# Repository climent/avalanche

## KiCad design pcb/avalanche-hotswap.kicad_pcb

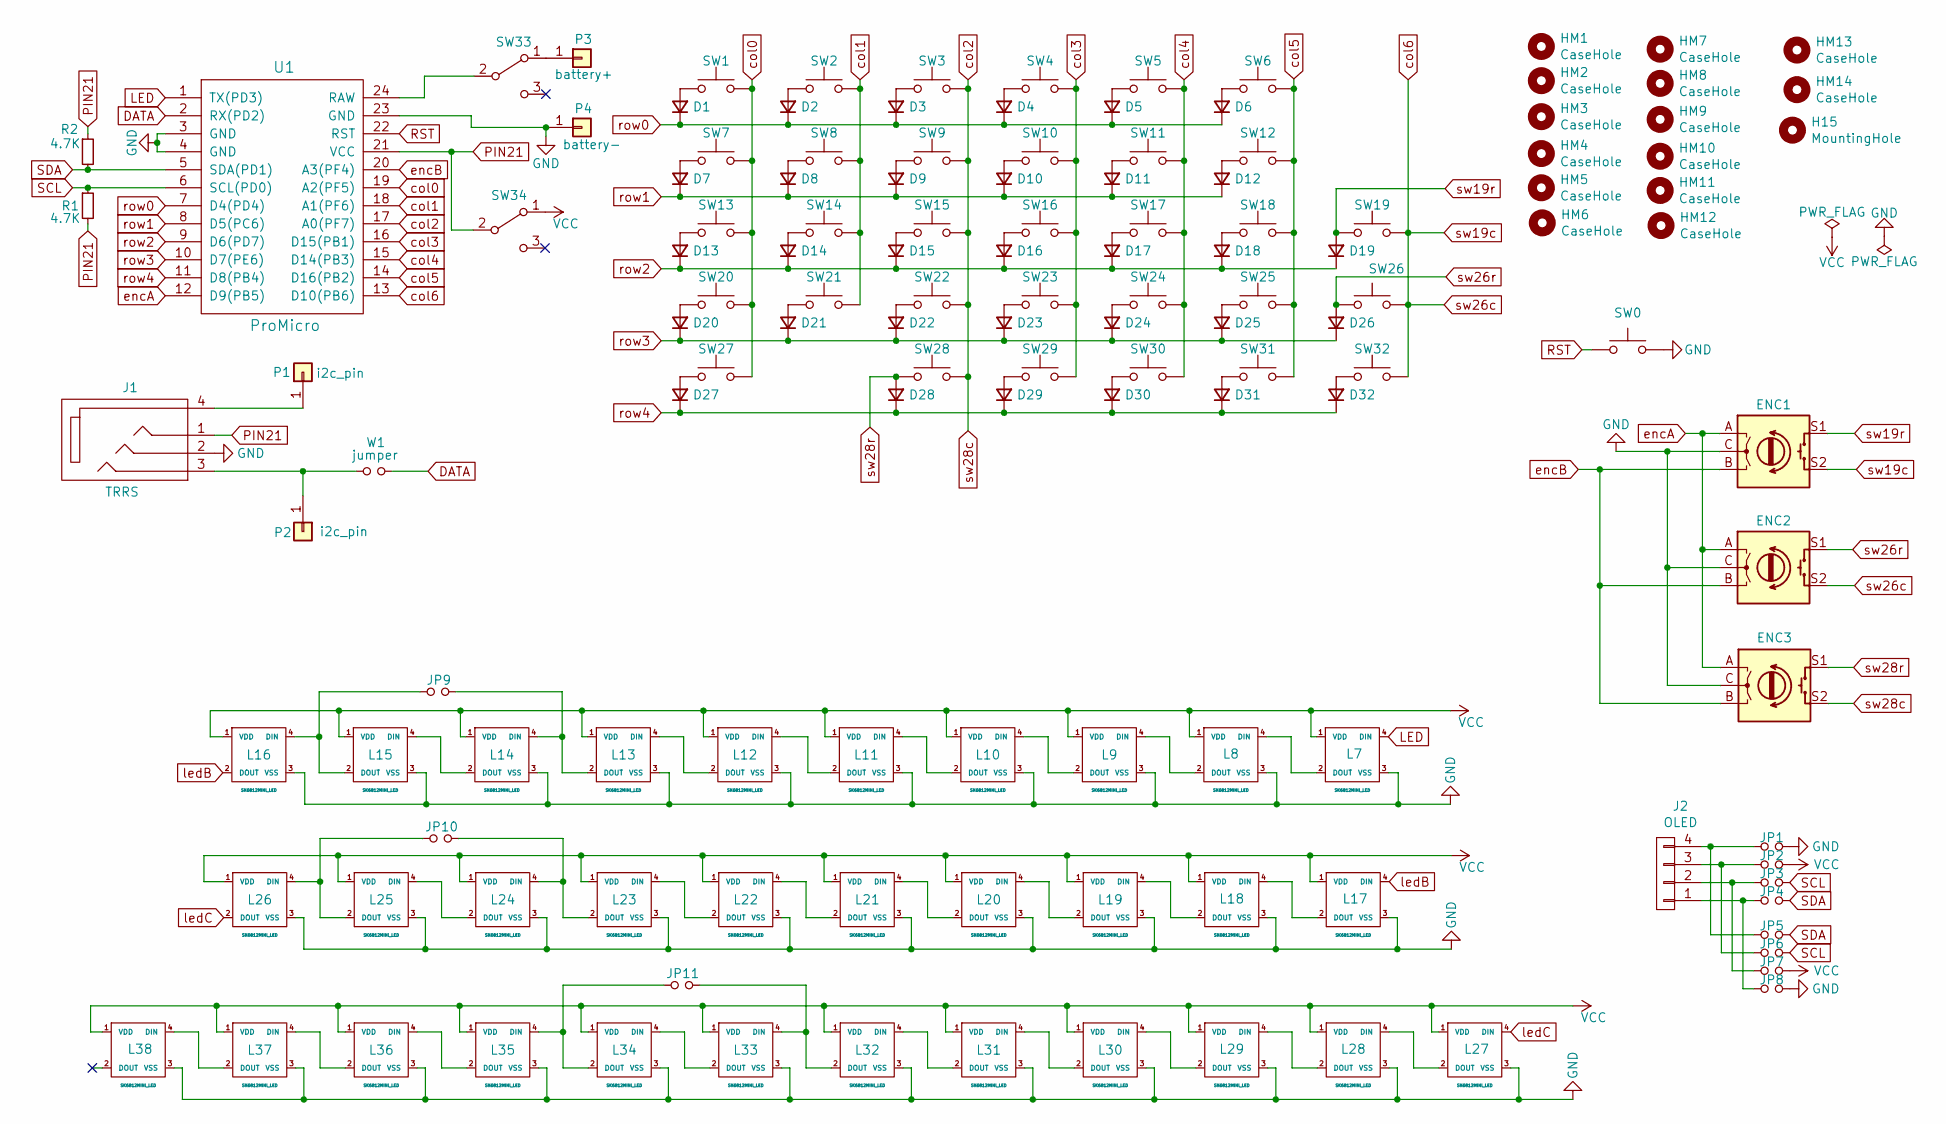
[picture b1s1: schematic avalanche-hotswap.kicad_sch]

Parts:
D1, D2, D3, D4, D5, D6, D7, D8, D9, D10, D11, D12, D13, D14, D15, D16, D17, D18, D19, D20, D21, D22, D23, D24, D25, D26, D27, D28, D29, D30, D31, D32: 1N4148; diode_TH_SMD
ENC1, ENC2, ENC3: Rotary_Encoder_Switch; RotaryEncoder_Alps_EC11E-Switch_Vertical_H20mm-keebio_modif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
H15: MountingHole; M2_HOLE_PCB
HM1, HM2, HM3, HM4, HM5, HM6, HM7, HM8, HM9, HM10, HM11, HM12, HM13, HM14: CaseHole; M2_HOLE_PCB
J1: TRRS; MJ-4PP-9
J2: OLED; OLED_4Pin_SSD1306
JP1, JP2, JP3, JP4, JP5, JP6, JP7, JP8: Device_Jumper_NO_Small; avalanche_Jumper
JP9, JP10, JP11: Device_Jumper_NO_Small; Jumper_rev
L7, L8, L9, L10, L11, L12, L13, L14, L15, L16, L17, L18, L19, L20, L21, L22, L23, L24, L25, L26, L27, L28, L29, L30, L31, L32, L33, L34, L35, L36, L37, L38: SK6812MINI_LED; YS-SK6812MINI-E
P1, P2: i2c_pin; 1pin_conn
P3: battery+; 1pin_conn
P4: battery-; 1pin_conn
R1, R2: 4.7K; Resistor_Hybrid_1205
SW0: SW_Push; Switch_Reset_THT
SW1, SW2, SW3, SW4, SW5, SW6, SW7, SW8, SW9, SW10, SW11, SW12, SW13, SW14, SW15, SW16, SW17, SW18, SW19, SW20, SW21, SW22, SW23, SW24, SW25, SW26, SW27, SW28, SW29, SW30, SW31, SW32: SW_Push; CherryMX_MidHeight_Hotswap_1u
SW33, SW34: SW_DPDT_x2; Switch_MSK-12C01-07
U1: ProMicro; ProMicro_rev2
W1: jumper; avalanche_Jumper

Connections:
DATA: U1.2 (RX(PD2)), W1.1
GND: ENC1.C, ENC2.C, ENC3.C, J1.2, JP1.2, JP8.2, L7.3 (VSS), L8.3 (VSS), L9.3 (VSS), L10.3 (VSS), L11.3 (VSS), L12.3 (VSS), L13.3 (VSS), L14.3 (VSS), L15.3 (VSS), L16.3 (VSS), L17.3 (VSS), L18.3 (VSS), L19.3 (VSS), L20.3 (VSS), L21.3 (VSS), L22.3 (VSS), L23.3 (VSS), L24.3 (VSS), L25.3 (VSS), L26.3 (VSS), L27.3 (VSS), L28.3 (VSS), L29.3 (VSS), L30.3 (VSS), L31.3 (VSS), L32.3 (VSS), L33.3 (VSS), L34.3 (VSS), L35.3 (VSS), L36.3 (VSS), L37.3 (VSS), L38.3 (VSS), P4.1, SW0.2, U1.3 (GND), U1.4 (GND), U1.23 (GND)
LED: L7.4 (DIN), U1.1 (TX(PD3))
unnamed: D1.2 (A), SW1.1
unnamed: D2.2 (A), SW2.1
unnamed: D3.2 (A), SW3.1
unnamed: D4.2 (A), SW4.1
unnamed: D5.2 (A), SW5.1
unnamed: D6.2 (A), SW6.1
unnamed: D7.2 (A), SW7.1
unnamed: D8.2 (A), SW8.1
unnamed: D9.2 (A), SW9.1
unnamed: D10.2 (A), SW10.1
unnamed: D11.2 (A), SW11.1
unnamed: D12.2 (A), SW12.1
unnamed: D13.2 (A), SW13.1
unnamed: D14.2 (A), SW14.1
unnamed: D15.2 (A), SW15.1
unnamed: D16.2 (A), SW16.1
unnamed: D17.2 (A), SW17.1
unnamed: D18.2 (A), SW18.1
unnamed: D20.2 (A), SW20.1
unnamed: D21.2 (A), SW21.1
unnamed: D22.2 (A), SW22.1
unnamed: D23.2 (A), SW23.1
unnamed: D24.2 (A), SW24.1
unnamed: D25.2 (A), SW25.1
unnamed: D27.2 (A), SW27.1
unnamed: D29.2 (A), SW29.1
unnamed: D30.2 (A), SW30.1
unnamed: D31.2 (A), SW31.1
unnamed: D32.2 (A), SW32.1
unnamed: J1.3, P2.1, W1.2
unnamed: J1.4, P1.1
unnamed: J2.1, JP4.1, JP8.1
unnamed: J2.2, JP3.1, JP7.1
unnamed: J2.3, JP2.1, JP6.1
unnamed: J2.4, JP1.1, JP5.1
unnamed: JP9.1, L15.2 (DOUT), L16.4 (DIN)
unnamed: JP9.2, L13.2 (DOUT), L14.4 (DIN)
unnamed: JP10.1, L25.2 (DOUT), L26.4 (DIN)
unnamed: JP10.2, L23.2 (DOUT), L24.4 (DIN)
unnamed: JP11.1, L34.2 (DOUT), L35.4 (DIN)
unnamed: JP11.2, L32.2 (DOUT), L33.4 (DIN)
unnamed: L7.2 (DOUT), L8.4 (DIN)
unnamed: L8.2 (DOUT), L9.4 (DIN)
unnamed: L10.2 (DOUT), L11.4 (DIN)
unnamed: L9.2 (DOUT), L10.4 (DIN)
unnamed: L11.2 (DOUT), L12.4 (DIN)
unnamed: L12.2 (DOUT), L13.4 (DIN)
unnamed: L14.2 (DOUT), L15.4 (DIN)
unnamed: L17.2 (DOUT), L18.4 (DIN)
unnamed: L18.2 (DOUT), L19.4 (DIN)
unnamed: L19.2 (DOUT), L20.4 (DIN)
unnamed: L20.2 (DOUT), L21.4 (DIN)
unnamed: L21.2 (DOUT), L22.4 (DIN)
unnamed: L22.2 (DOUT), L23.4 (DIN)
unnamed: L24.2 (DOUT), L25.4 (DIN)
unnamed: L27.2 (DOUT), L28.4 (DIN)
unnamed: L28.2 (DOUT), L29.4 (DIN)
unnamed: L29.2 (DOUT), L30.4 (DIN)
unnamed: L30.2 (DOUT), L31.4 (DIN)
unnamed: L31.2 (DOUT), L32.4 (DIN)
unnamed: L33.2 (DOUT), L34.4 (DIN)
unnamed: L35.2 (DOUT), L36.4 (DIN)
unnamed: L36.2 (DOUT), L37.4 (DIN)
unnamed: L37.2 (DOUT), L38.4 (DIN)
unnamed: P3.1, SW33.1 (A)
unnamed: SW33.2 (B), U1.24 (RAW)
PIN21: J1.1, R1.2, R2.1, SW34.2 (B), U1.21 (VCC)
RST: SW0.1, U1.22 (RST)
SCL: JP3.2, JP6.2, R1.1, U1.6 (SCL(PD0))
SDA: JP4.2, JP5.2, R2.2, U1.5 (SDA(PD1))
VCC: JP2.2, JP7.2, L7.1 (VDD), L8.1 (VDD), L9.1 (VDD), L10.1 (VDD), L11.1 (VDD), L12.1 (VDD), L13.1 (VDD), L14.1 (VDD), L15.1 (VDD), L16.1 (VDD), L17.1 (VDD), L18.1 (VDD), L19.1 (VDD), L20.1 (VDD), L21.1 (VDD), L22.1 (VDD), L23.1 (VDD), L24.1 (VDD), L25.1 (VDD), L26.1 (VDD), L27.1 (VDD), L28.1 (VDD), L29.1 (VDD), L30.1 (VDD), L31.1 (VDD), L32.1 (VDD), L33.1 (VDD), L34.1 (VDD), L35.1 (VDD), L36.1 (VDD), L37.1 (VDD), L38.1 (VDD), SW34.1 (A)
col0: SW1.2, SW7.2, SW13.2, SW20.2, SW27.2, U1.19 (A2(PF5))
col1: SW2.2, SW8.2, SW14.2, SW21.2, U1.18 (A1(PF6))
col2: ENC3.S2, SW3.2, SW9.2, SW15.2, SW22.2, SW28.2, U1.17 (A0(PF7))
col3: SW4.2, SW10.2, SW16.2, SW23.2, SW29.2, U1.16 (D15(PB1))
col4: SW5.2, SW11.2, SW17.2, SW24.2, SW30.2, U1.15 (D14(PB3))
col5: SW6.2, SW12.2, SW18.2, SW25.2, SW31.2, U1.14 (D16(PB2))
col6: ENC1.S2, ENC2.S2, SW19.2, SW26.2, SW32.2, U1.13 (D10(PB6))
encA: ENC1.A, ENC2.A, ENC3.A, U1.12 (D9(PB5))
encB: ENC1.B, ENC2.B, ENC3.B, U1.20 (A3(PF4))
ledB: L16.2 (DOUT), L17.4 (DIN)
ledC: L26.2 (DOUT), L27.4 (DIN)
row0: D1.1 (K), D2.1 (K), D3.1 (K), D4.1 (K), D5.1 (K), D6.1 (K), U1.7 (D4(PD4))
row1: D7.1 (K), D8.1 (K), D9.1 (K), D10.1 (K), D11.1 (K), D12.1 (K), U1.8 (D5(PC6))
row2: D13.1 (K), D14.1 (K), D15.1 (K), D16.1 (K), D17.1 (K), D18.1 (K), D19.1 (K), U1.9 (D6(PD7))
row3: D20.1 (K), D21.1 (K), D22.1 (K), D23.1 (K), D24.1 (K), D25.1 (K), D26.1 (K), U1.10 (D7(PE6))
row4: D27.1 (K), D28.1 (K), D29.1 (K), D30.1 (K), D31.1 (K), D32.1 (K), U1.11 (D8(PB4))
sw19r: D19.2 (A), ENC1.S1, SW19.1
sw26r: D26.2 (A), ENC2.S1, SW26.1
sw28r: D28.2 (A), ENC3.S1, SW28.1

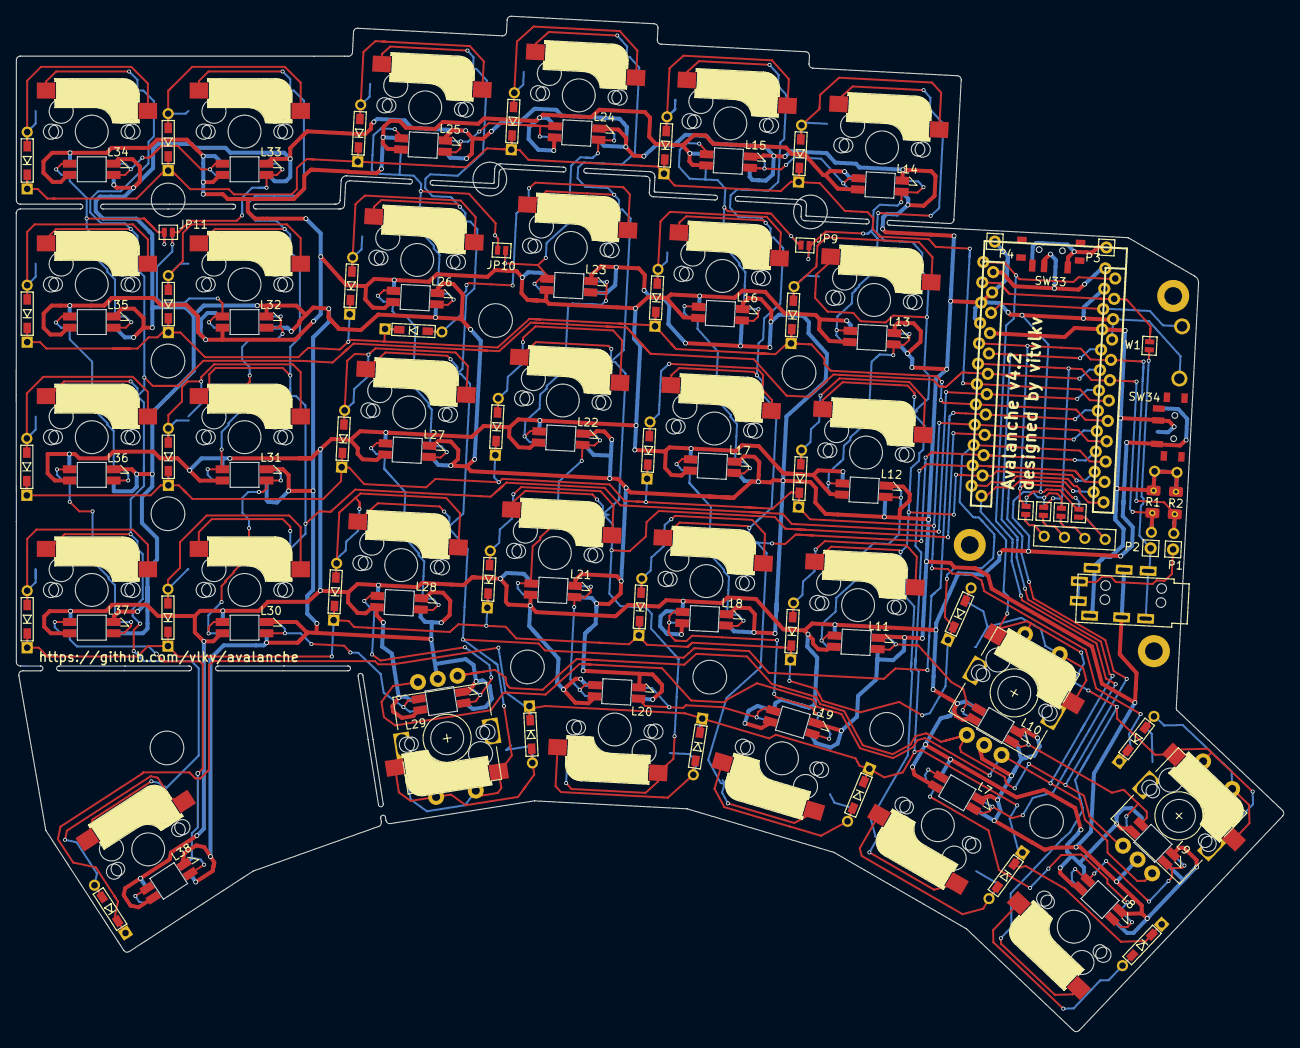
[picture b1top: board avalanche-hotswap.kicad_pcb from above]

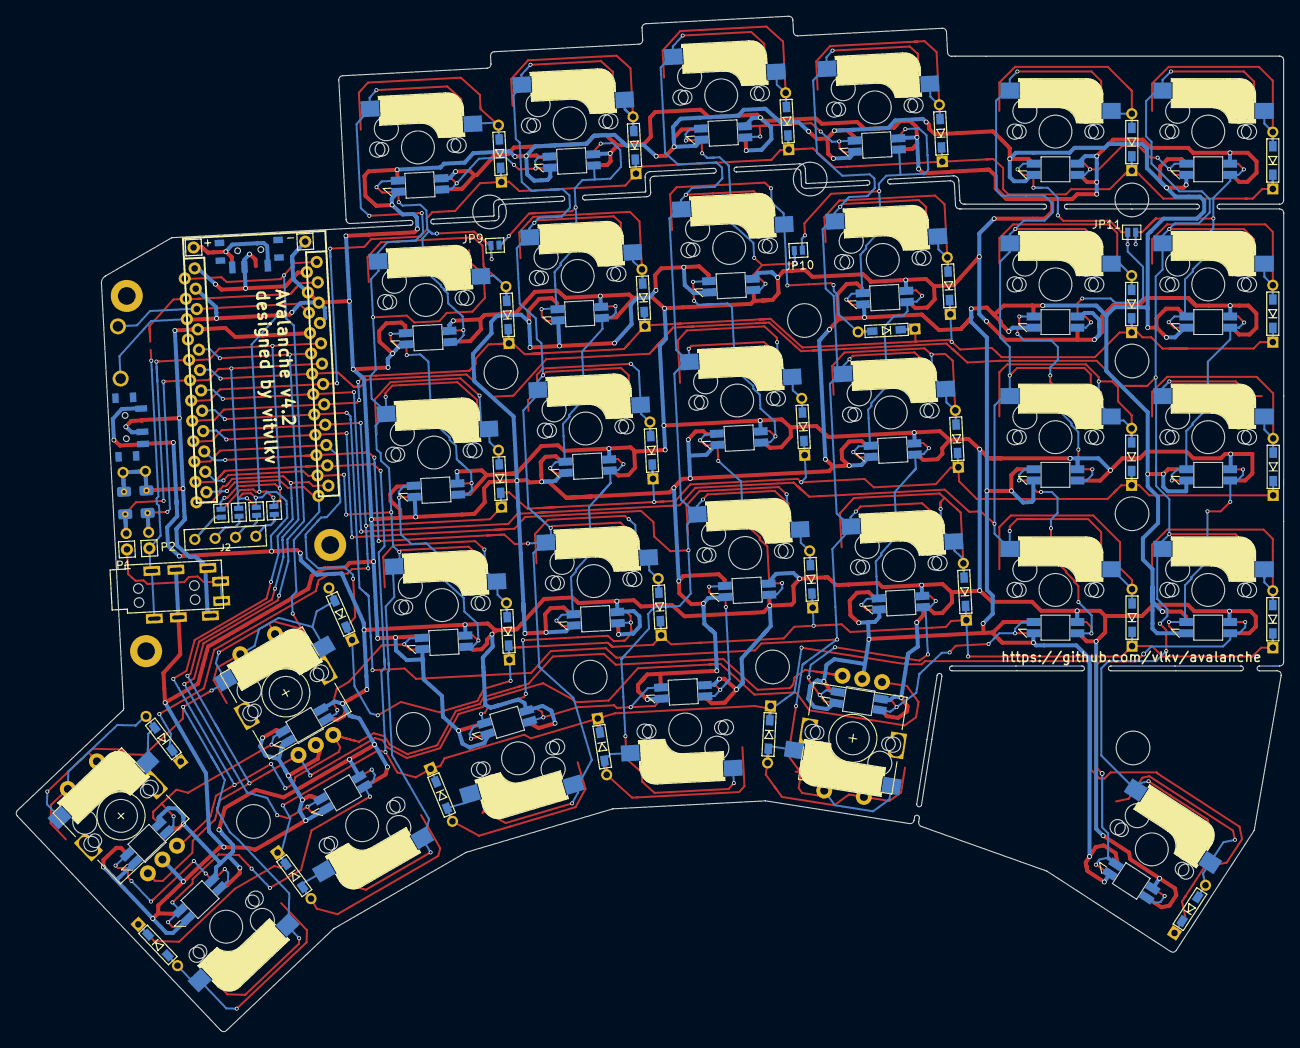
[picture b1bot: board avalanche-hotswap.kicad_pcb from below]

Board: 2 copper layers, 158.0 x 126.6 mm, 138 parts (5 on the bottom side), 93 nets.

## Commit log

2021-12-03 Modifications to have the palm key.
2021-12-11 Avalanche with palm key.
2021-12-11 Merged v4.2 into palm branch.
2022-03-27 New Snowslide unsplit board.
2022-04-03 Added .gitignore
2022-04-03 PCB layout completed.
2022-05-20 Checkpoint commit with merge from upstream.
2022-06-06 Checkpoint commit.
2022-07-03 Completed board and case.
2022-07-11 Updated PCB and gerber files.
2022-08-06 Fixed schematic and PCB for horrible mistake with row connections.
2022-08-27 Modded the board to have no encoders.
2023-04-13 Final changes of palm release.
